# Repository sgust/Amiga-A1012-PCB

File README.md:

This is a small PCB board for my Amiga A1012 double floppy project.

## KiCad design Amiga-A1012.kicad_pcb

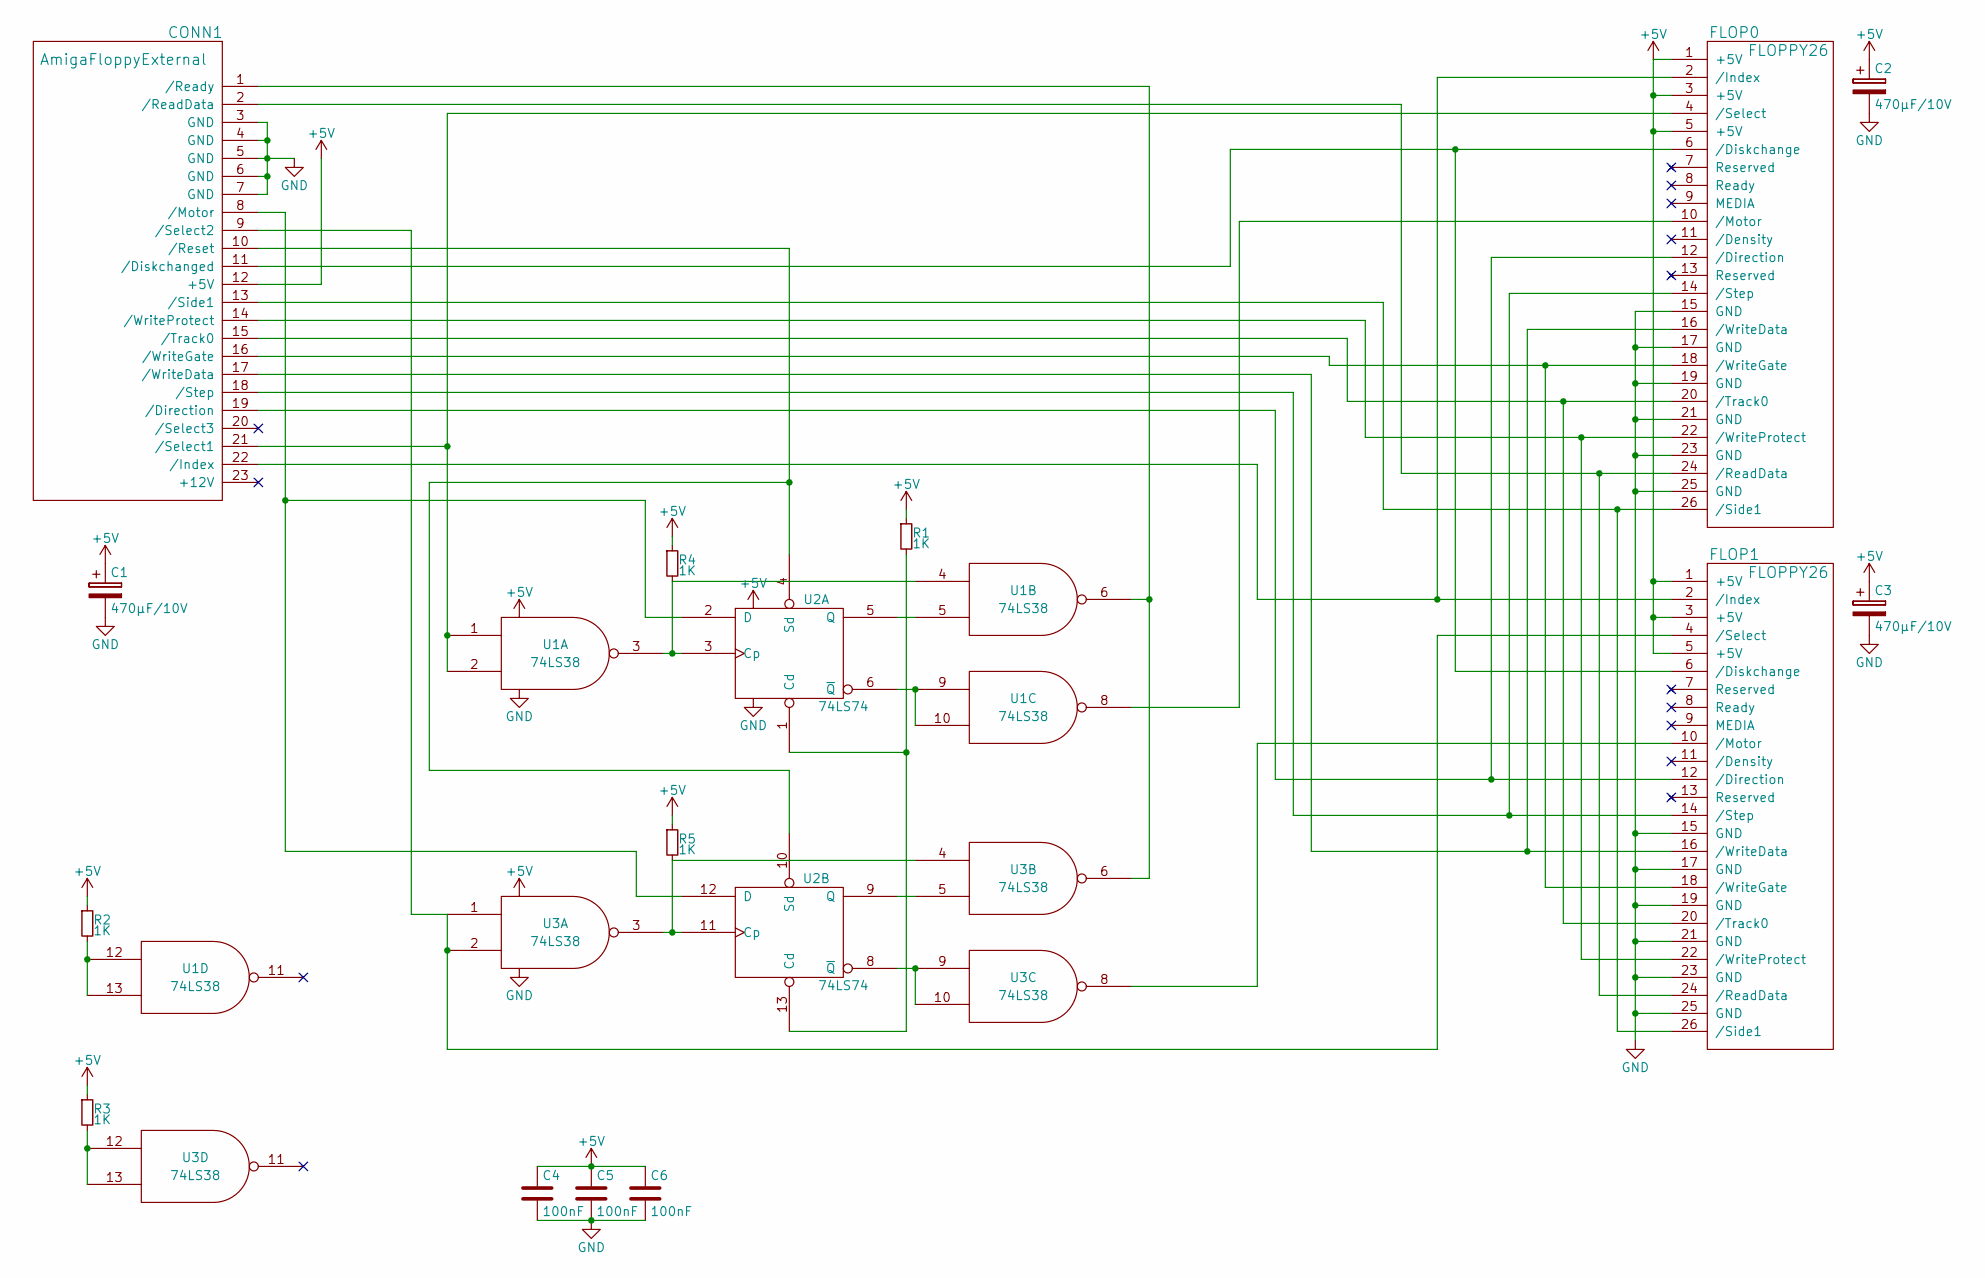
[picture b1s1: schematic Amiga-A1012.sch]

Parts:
C1, C2, C3: 470µF/10V; Tantalum_Case-D_EIA-7343-31_Reflow
C4, C5, C6: 100nF; R_0603
CONN1: AmigaFloppyExternal; Pin_Header_Angled_2x12
FLOP0, FLOP1: FLOPPY26; FFC-26
R1, R2, R3, R4, R5: 1K; R_0603
U1, U3: 74LS38; SOIC-14_N
U2: 74LS74; SOIC-14_N

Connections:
+5V: C1.1, C2.1, C3.1, C4.1, C5.1, C6.1, CONN1.12 (+5V), FLOP0.1 (+5V), FLOP0.3 (+5V), FLOP0.5 (+5V), FLOP1.1 (+5V), FLOP1.3 (+5V), FLOP1.5 (+5V), R1.1, R2.1, R3.1, R4.1, R5.1, U1.14 (VCC), U2.14 (VCC), U3.14 (VCC)
GND: C1.2, C2.2, C3.2, C4.2, C5.2, C6.2, CONN1.3 (GND), CONN1.4 (GND), CONN1.5 (GND), CONN1.6 (GND), CONN1.7 (GND), FLOP0.15 (GND), FLOP0.17 (GND), FLOP0.19 (GND), FLOP0.21 (GND), FLOP0.23 (GND), FLOP0.25 (GND), FLOP1.15 (GND), FLOP1.17 (GND), FLOP1.19 (GND), FLOP1.21 (GND), FLOP1.23 (GND), FLOP1.25 (GND), U1.7 (GND), U2.7 (GND), U3.7 (GND)
unnamed: CONN1.1 (/Ready), U1.6, U3.6
unnamed: CONN1.2 (/ReadData), FLOP0.24 (/ReadData), FLOP1.24 (/ReadData)
unnamed: CONN1.8 (/Motor), U2.2 (D), U2.12 (D)
unnamed: CONN1.9 (/Select2), FLOP1.4 (/Select), U3.1, U3.2
unnamed: CONN1.10 (/Reset), U2.4 (Sd), U2.10 (Sd)
unnamed: CONN1.11 (/Diskchanged), FLOP0.6 (/Diskchange), FLOP1.6 (/Diskchange)
unnamed: CONN1.13 (/Side1), FLOP0.26 (/Side1), FLOP1.26 (/Side1)
unnamed: CONN1.14 (/WriteProtect), FLOP0.22 (/WriteProtect), FLOP1.22 (/WriteProtect)
unnamed: CONN1.15 (/Track0), FLOP0.20 (/Track0), FLOP1.20 (/Track0)
unnamed: CONN1.16 (/WriteGate), FLOP0.18 (/WriteGate), FLOP1.18 (/WriteGate)
unnamed: CONN1.17 (/WriteData), FLOP0.16 (/WriteData), FLOP1.16 (/WriteData)
unnamed: CONN1.18 (/Step), FLOP0.14 (/Step), FLOP1.14 (/Step)
unnamed: CONN1.19 (/Direction), FLOP0.12 (/Direction), FLOP1.12 (/Direction)
unnamed: CONN1.21 (/Select1), FLOP0.4 (/Select), U1.1, U1.2
unnamed: CONN1.22 (/Index), FLOP0.2 (/Index), FLOP1.2 (/Index)
unnamed: FLOP0.10 (/Motor), U1.8
unnamed: FLOP1.10 (/Motor), U3.8
unnamed: R1.2, U2.1 (Cd), U2.13 (Cd)
unnamed: R2.2, U1.12, U1.13
unnamed: R3.2, U3.12, U3.13
unnamed: R4.2, U1.3, U1.4, U2.3 (Cp)
unnamed: R5.2, U2.11 (Cp), U3.3, U3.4
unnamed: U1.5, U2.5 (Q)
unnamed: U1.9, U1.10, U2.6 (~Q)
unnamed: U2.8 (~Q), U3.9, U3.10
unnamed: U2.9 (Q), U3.5

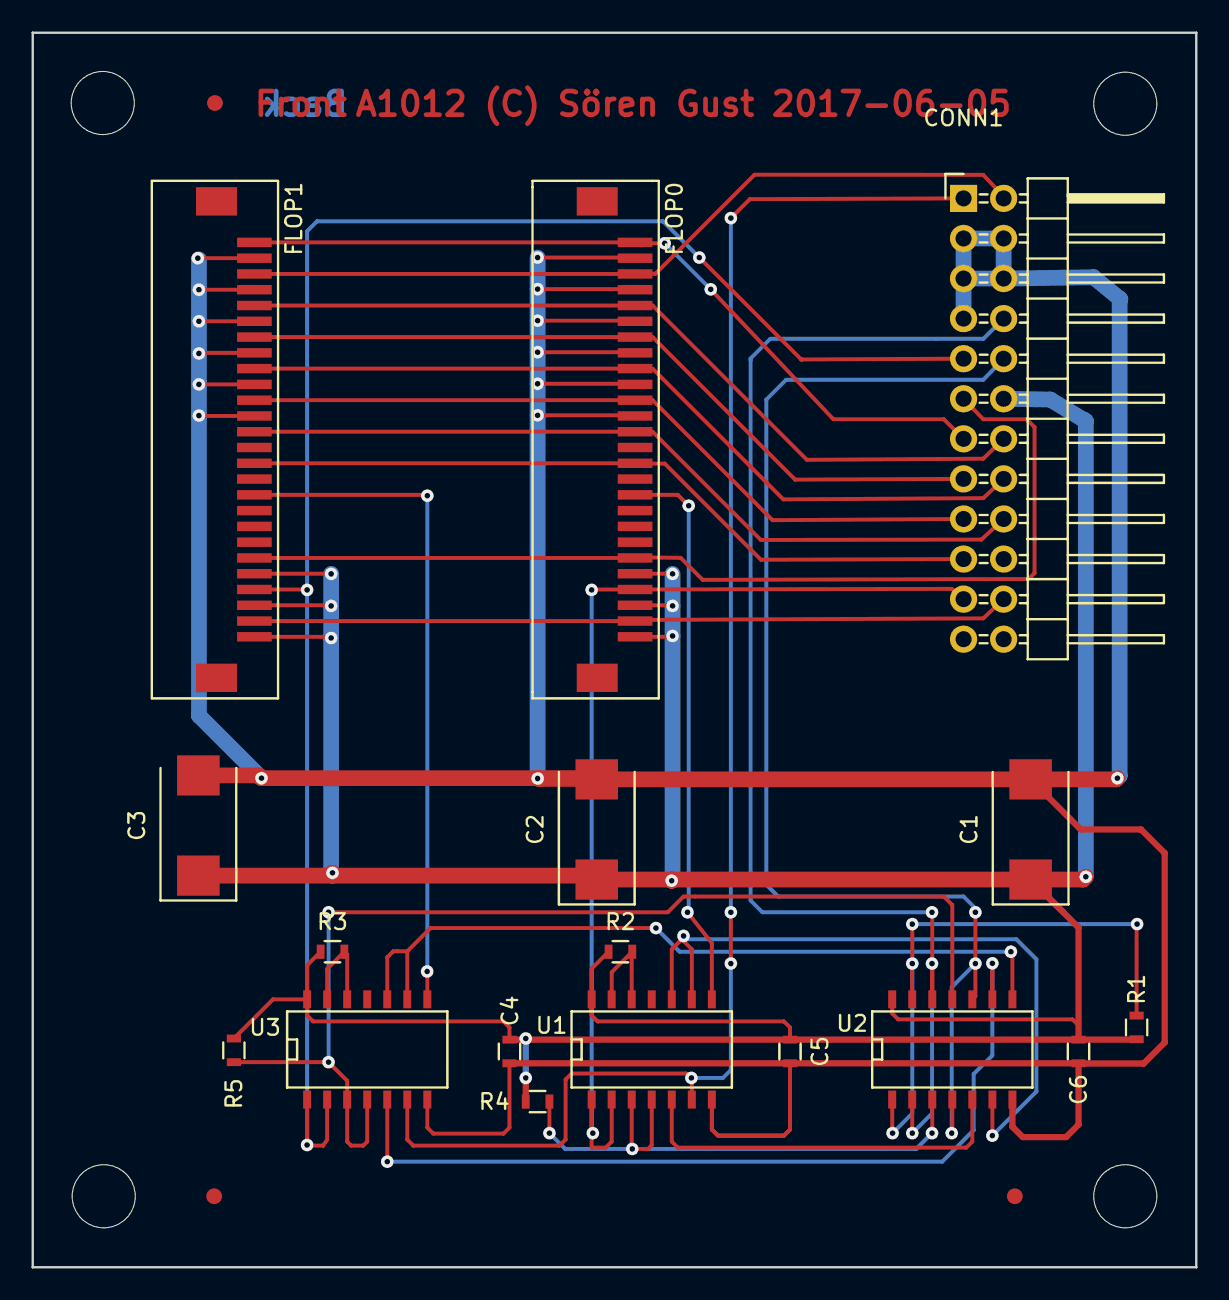
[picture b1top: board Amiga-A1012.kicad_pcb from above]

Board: 2 copper layers, 73.8 x 78.2 mm, 24 parts (0 on the bottom side), 28 nets.

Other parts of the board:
Hole1, Hole2, Hole3, Hole4: MountingHole_4mm
Marker1, Marker2, Marker3: Fiducial_1mm_Dia_2.54mm_Outer_CopperTop

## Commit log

2017-04-23 Initial commit: Schematic entry complete. Seperated components on board.
2017-04-23 Started placing and routing, only big caps and connectors.
2017-04-26 Added decoupling caps. More routing.
2017-04-27 More routing. Connected VCC to +5V net, for LS chips.
2017-04-29 Finished routing. Fixed routing problems with unconnected nets. Added fiducials.
2017-04-30 Added mounting holes, moved fiducials.
2017-04-30 Generated gerber.
2017-04-30 Store gerber files.
2017-04-30 Added Front/Back texts, added copyright/date.
2017-05-31 Work in progress, fixing problems found in prototype: * swapped clock and data on LS74 * need pull-up on LS38 to LS74 * add pull-ups on unused LS38 gates * connect drive reset
    Started to reduce size.
2017-06-05 Finished routing, board is much smaller now.
2017-06-05 Made all vias bigger to allow cheaper eurocircuits manufacturing.
2017-06-29 Removed gerber for old release.
2017-06-29 Added Würth number for floppy connector.
2017-06-29 Named holes and fiducials.
2017-06-29 Created gerber files.
2017-06-29 Created 2 different BOM files.
2017-06-29 Created minimal README.
2017-06-29 Added Schematic as PDF.
